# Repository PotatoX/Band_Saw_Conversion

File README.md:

# Band_Saw_Conversion

## Summary

Recently I needed (had an excuse to get) a band saw capable of cutting metal for a few of my projects. As with most of my projects/hobbies there are a number of outcomes I seek:

* Cheap
* Technical
* Build
* Learn

To this end I started shopping around to acquire a band saw as cheap as possible as it would only be used on a limited basis for hobby work. I need the saw to be able to cut metal and fit a small foot print on my bench. I wanted the saw to be vertical in order to minimize the space consumed as my bench and garage space is at a premium at this point.

With these constraints in mind I set my sights on a Harbor Freight 1/3 HP 9 in Benchtop Band Saw. I caught it on sale a Harbor Freight (w/ coupon) for right around $100. Similar saws can be found at your local big box stores.

Using this basic frame and some upgrades I have been able to convert this wood cutting vertical band saw to a metal cutting type with speed control and FPS display.

I now have a small band saw capable of cutting metal, wood, plastic, etc. that fits on the corner of my bench.

This project encompass the conversion and in indented to share the process with other makers. If you have questions, need additional details, or see any bugs please let me know.

The entire project can be found on [GitHub](https://github.com/PotatoX/Band_Saw_Conversion/). Consider contributing and making it even better if you happen to create other customizations.

Additionally, I will list parts used in this project on my [OpenBazzar store](https://openbazaar.com/store/QmVFRGwApdcef56Be7FPXnXQaB79rYrve3otFsrWvSwbAu).

## Design Choices
Thnking ack thrpugh the steps taken from the begining to end; a text book design process was not followed, rather a development and refine!emt from blade to display.

### The Blade
There the first choice was to find a blade that fit and was capable of cutting metalss (steel). By default the saw comes equiped woth a wood cutting 62in blade, carbon steel, 7 Teeth per Inch (*TPI*), 1/8in wide. I had found a couple of reports online that indicate success cutting plastic and aluminium, so long as a gentle touch was used. clearly the default blade had no chance of taking on steels.

Therefore the search began for a suitable bimetal blade. Most of my local stores carried various blades, some bimetal, but none in the 62in size. 62in appears to be a bit of a *custom* size. when local stores fail Amazon.com often saves the day. After scrolling though lists of blades I was able to to find a suitable blade; 62in, bimetal, 1/2in, 14 TPI.

[Imachinist S621214 62-inch X 1/2-inch X 14 TPI Bi-metal Band Saw Blades](https://www.amazon.com/gp/product/B010G9IJG6)

The next challenge was to find a way to drive the blade @ ~300 FPM for Steel, 600ish FPM for Aluminum, and 2000 FPM for Wood. Looking at the stock motor it was designed to drive the blade at 2460 FPM and is not adjustable. Further the motor is an induction motor which can not be speed controlled without a frequency drive, and even with one, would loose power proportional to the reduction in frequency; meaning at slow speeds is would lose power.

Therefore, a SCR controlled DC motor setup was needed. Given the *Cheap* requirement I scrubed ebay for a cheap DC motor. I found that used DC motors from tredmills seem to be abundent and are therefore reasonably priced. I found mine for ~$30.

A small bracket had to be made to adapat the motor to the band saw frame

In order to control the motor I found a generic SCR speed control. The exact feature of the SCR were not necessary to specify other than it needed to be able to handle sufficient power. 4000W was probably over kill, but rather more than not enough, and given the price for smaller units was roughly the same, this did the trick.

The SCR needed a couple of mods to fine tune the upper and lower speed bounds. This is expanded on more in in the electronics section.

In order to install the motor I had a to get small belt pully mate to the motor.

I then needed an clean way to mount the SCR on the frame which led to the need to design an enclosure to house and mount the SCR.

I figured, if I am going to make a custom enclosure might as well make a display to disply the FPM of the blade; I mean I've come this far, why not.

Lastely I designed a small board which reads a hall sensor on the back of the motor, then converts the motor shaft speed to FPM, and displays this on a small 7-Segment output. 

## The Physical Form

### Hardware
The enclosure has been modeled in Onshape, source files can be found [here](https://cad.onshape.com/documents/ca0881e1177c075414a017b7/w/e514d8a98751ae0bca0296ff/e/90af0d38bd02678226dfc615).

If you are in need of a 3D printed enclosure, let me know and I will be happy to add them to my [OpenBazzar store](https://openbazaar.com/store/QmVFRGwApdcef56Be7FPXnXQaB79rYrve3otFsrWvSwbAu).

### Electronics

#### SCR Modifications
Unfortunately I forgot to take pictures while modifing the SCR. If you get a generic SCR you simply have to swap out the the potentiometer some one that is of a range more appropraite for the speeds you whish to operate at. This will be SCR and motor dependent. In my case I added a 33k resistor in series with a 50K pot.

#### Hall Effect Sensor
The hall effect sensor I used was an A3141 IC. This worked for my setup given the magnet I used and its location on the rear portion of the motor shaft. Any hall effect sensor in this family should do the trick.

[Datasheet](https://github.com/PotatoX/Band_Saw_Conversion/blob/master/Electronics/KiCad/Tachometer/Datasheets/A3141-2-3-4-Datasheet.pdf)

#### Tachometer Board
The design has been complete in KiCad. Input either 120V AC or 6V-12V DC. Board can be but down to remove AC section if DC is used. I have excess boards that will be listed on my [OpenBazzar store](https://openbazaar.com/store/QmVFRGwApdcef56Be7FPXnXQaB79rYrve3otFsrWvSwbAu) along with some of the odd components.

If you need a component not currently listed, let me know and I will be happy to add them to my [OpenBazzar store](https://openbazaar.com/store/QmVFRGwApdcef56Be7FPXnXQaB79rYrve3otFsrWvSwbAu) along with some of the odd components..

### Software
[Arduino firmware can be found here.](https://github.com/PotatoX/Band_Saw_Conversion/tree/master/Software/Arduino/Tachometer_Rev_A)

#### Calculation of Slope
There are a couple of ways to calculate the correct [slope value](https://github.com/PotatoX/Band_Saw_Conversion/blob/c9c9d59a0e278d77ea138ab6ab9a776811436fa7/Software/Arduino/Tachometer_Rev_A/Tachometer_Rev_A.ino#L35) for the firmware:

##### Method 1 - Experimentation w/ Tachometer
This method requires a [contactless tachometer](https://www.aliexpress.com/item/2017-Hot-Selling-NEW-Digital-Laser-Photo-Tachometer-Non-Contact-RPM-Tach-Speed-Gauge-Engine-High/32827623720.html).

1. Initially set the slope to 1 and flash the controller.
2. Connect the controller board to the saw and verify proper operation
3. Measure the diameter of one of your blade drive wheels.

4. Place a tachometer reflector on the blade drive wheel and test that stable RPM readings can be taken. **DANGER - _As the cover to the saw is open in order to take this measurement take extream care to be as far away from the blade as possible, and allow yourself multiple options for escape and power shut off incase the blade should come off the drive wheels._**
5. Start the band saw at a low speed and record both the reading on the controller and the reading on the tachometer.
6. Repeat measurements various times in order to take readings through out the intended operating speed range.
7. Using a [spreadsheet](https://github.com/PotatoX/Band_Saw_Conversion/blob/master/Software/Arduino/Tachometer_Rev_A/BandSaw%20Slope%20Calculations.ods?raw=true) convert the tachometer readings to SFM
8. Using a [spreadsheet](https://github.com/PotatoX/Band_Saw_Conversion/blob/master/Software/Arduino/Tachometer_Rev_A/BandSaw%20Slope%20Calculations.ods?raw=true) plot the controller readings vs the SFM(tachometer readings).
10. Generate a linear fit, note the slope of the fit equation.
11. Input the slope into the firmware of the controller and re-flash. The controller should now read in SFM.

##### Method 2 - Ratio Calculations
1. Measure the diameter of one of your blade drive wheels.

2. Count the teeth of the motor pully and the blade wheel pully.
3. Enter the all values in the [spreadsheet](https://github.com/PotatoX/Band_Saw_Conversion/blob/master/Software/Arduino/Tachometer_Rev_A/BandSaw%20Slope%20Calculations.ods?raw=true).
4. Input the slope into the firmware of the controller and flash. The controller should now read in SFM.

# Support Projects Like This
You can support projects like this by using my [OpenBazzar store](https://openbazaar.com/store/QmVFRGwApdcef56Be7FPXnXQaB79rYrve3otFsrWvSwbAu). Like all hobbies, ones that are self-funded are always easier progress.

# Safety/Disclaimer
I am furnishing this item/content "as is". I do not provide any warranty of the item/content whatsoever, whether express, implied, or statutory, including, but not limited to, any warranty of merchantability or fitness for a particular purpose or any warranty that the contents of the item/content will be error-free.

In no respect shall I incur any liability for any damages, including, but limited to, direct, indirect, special, or consequential damages arising out of, resulting from, or any way connected to the use of the item, whether or not based upon warranty, contract, tort, or otherwise; whether or not injury was sustained by persons or property or otherwise; and whether or not loss was sustained from, or arose out of, the results of, the item/content, or any services that may be provided herein.

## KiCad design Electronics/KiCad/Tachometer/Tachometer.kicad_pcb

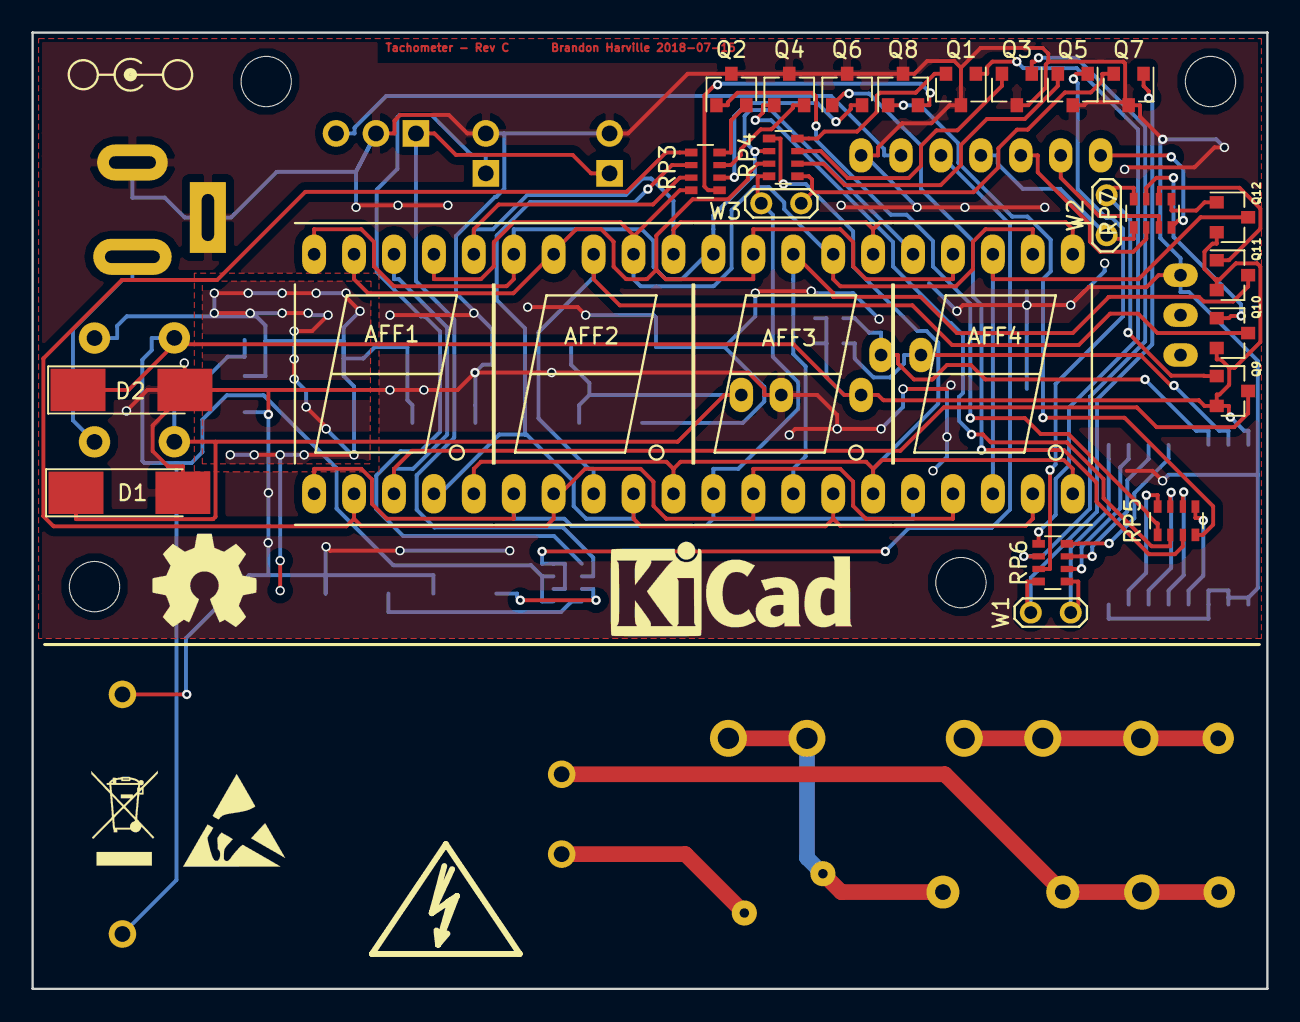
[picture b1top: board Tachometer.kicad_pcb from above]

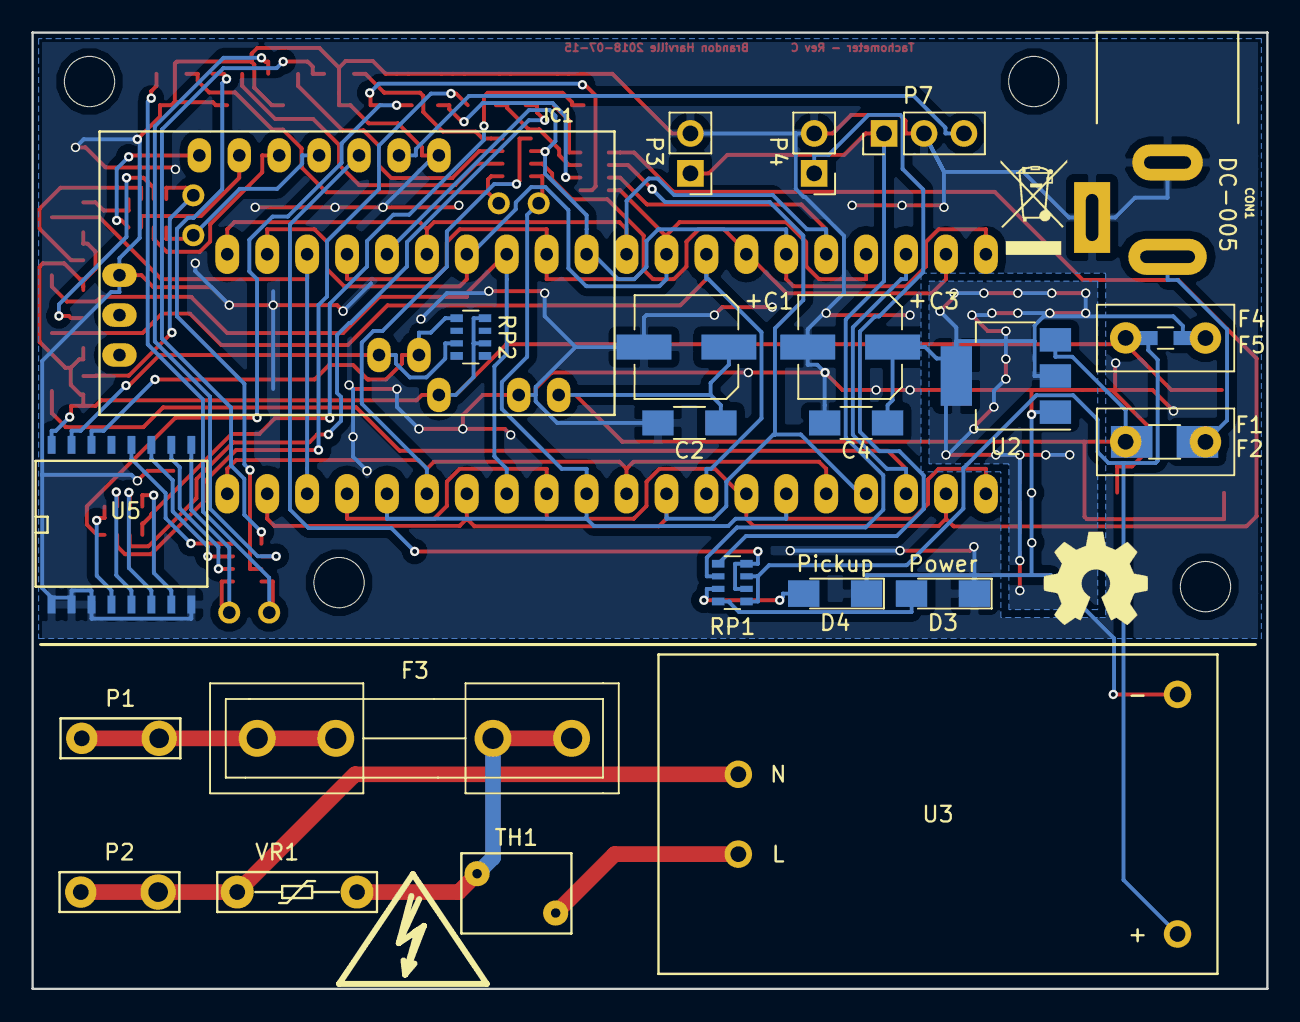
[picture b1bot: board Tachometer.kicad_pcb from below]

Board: 2 copper layers, 78.5 x 60.8 mm, 55 parts (25 on the bottom side), 61 nets.

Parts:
AFF1, AFF2, AFF3, AFF4: LTS-6960HR; 7SegmentLED_LTS6760_LTS6780
C1, C3: 10uF; CP_Elec_6.3x5.3
C2, C4: 22uF; C_1206_HandSoldering
CON1: DC-005; ADC-002
D1: 12V; D_MELF_Handsoldering
D2: 5.1V; D_MELF_Handsoldering
D3: Power; LED_1206_HandSoldering
D4: Pickup; LED_1206_HandSoldering
F1: 1A; Fuse_TE5_Littlefuse-395Series
F2: 2A 16V; Fuse_SMD1206_HandSoldering
F3: 1000mA; Fuseholder5x20_horiz_open_inline_Type-I
F4: 500mA; R_0603_HandSoldering
F5: 500mA; Fuse_TE5_Littlefuse-395Series
IC1: ArduinoProMini; pro_mini
M1, M2, M3, M4: MountingHole_3.2mm_M3_DIN965
P1, P2: CONN_01X01; Male_Terminal_Spade_Connector_6.3_Wide_5.08mm_Pins
P3, P4: CONN_01X02; Pin_Header_Straight_1x02_Pitch2.54mm
P7: CONN_01X03; Pin_Header_Straight_1x03_Pitch2.54mm
Q1, Q2, Q3, Q4, Q5, Q6, Q7, Q8, Q9, Q10, Q11, Q12: MMBT3906; SOT-23
RP1: 150; R_Array_Convex_4x0603
RP2: 10K; R_Array_Convex_4x0603
RP3, RP4: 91; R_Array_Convex_4x0603
RP5, RP6: 100; R_Array_Convex_4x0603
RP7: 510; R_Array_Convex_4x0603
TH1: NTC 5D-7; RV_Disc_D7_W5.1_P5
U2: LM1117-5.0; SOT-223-3_TabPin2
U3: TSP-05; TSP
U5: PCF8574; SO-16-W
VR1: 14D241K 240V; VARISTOR_MCIGICM_14D241K_240V
W1, W2, W3: TEST; Test_Point_2Pads

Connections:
/5V_REG: D2.1, F4.2, F5.2, IC1.21, Q9.2, Q10.2, Q11.2, Q12.2, RP1.1, RP1.3, RP2.2, RP2.4, U3.3, U5.16
/DC_IN: C1.1, C2.1, D1.1, F1.2, F2.2, IC1.24, U2.3
/GND: C1.2, C2.2, C3.2, C4.2, CON1.2, CON1.3, D1.2, D2.2, D3.1, D4.1, IC1.4, IC1.23, IC1.29, P3.2, P4.2, P7.2, Q1.3, Q2.3, Q3.3, Q4.3, Q5.3, Q6.3, Q7.3, Q8.3, U2.1, U3.4, U5.1, U5.2, U5.3, U5.8
/M_LIVE: F3.1, P1.1
/M_NEUTRAL: P2.1, U3.2, VR1.1
unnamed: AFF1.1, AFF2.1, AFF3.1, AFF4.1, RP4.8, W3.2
unnamed: AFF1.2, AFF2.2, AFF3.2, AFF4.2, RP3.5
unnamed: AFF1.3, AFF1.8, Q9.3
unnamed: AFF1.4, AFF2.4, AFF3.4, AFF4.4, RP3.6
unnamed: AFF1.5, AFF2.5, AFF3.5, AFF4.5, RP4.5
unnamed: AFF1.6, AFF2.6, AFF3.6, AFF4.6, RP3.7
unnamed: AFF1.7, AFF2.7, AFF3.7, AFF4.7, RP3.8
unnamed: AFF1.9, AFF2.9, AFF3.9, AFF4.9, RP4.7
unnamed: AFF1.10, AFF2.10, AFF3.10, AFF4.10, RP4.6
unnamed: AFF2.3, AFF2.8, Q10.3
unnamed: AFF3.3, AFF3.8, Q11.3
unnamed: AFF4.3, AFF4.8, Q12.3
unnamed: C3.1, C4.1, F4.1, F5.1, U2.2
unnamed: CON1.1, F1.1, F2.1
unnamed: D3.2, RP1.8
unnamed: D4.2, RP1.7
unnamed: F3.2, TH1.2, VR1.2
unnamed: IC1.5, P7.3
unnamed: IC1.6, RP1.2, RP1.4
unnamed: IC1.7, RP7.1, W2.1
unnamed: IC1.8, RP7.2
unnamed: IC1.9, RP7.3
unnamed: IC1.10, RP7.4
unnamed: IC1.25, RP2.7, U5.15
unnamed: IC1.26, RP2.5, U5.14
unnamed: P3.1, P7.1, RP1.6
unnamed: P4.1, RP1.5
unnamed: Q1.1, RP6.1
unnamed: Q1.2, RP4.4
unnamed: Q2.1, RP5.1
unnamed: Q2.2, RP3.4
unnamed: Q3.1, RP6.2
unnamed: Q3.2, RP4.3
unnamed: Q4.1, RP5.2
unnamed: Q4.2, RP3.3
unnamed: Q5.1, RP6.3
unnamed: Q5.2, RP4.2
unnamed: Q6.1, RP5.3
unnamed: Q6.2, RP3.2
unnamed: Q7.1, RP6.4, W1.1
unnamed: Q7.2, RP4.1, W3.1
unnamed: Q8.1, RP5.4
unnamed: Q8.2, RP3.1
unnamed: Q9.1, RP7.8, W2.2
unnamed: Q10.1, RP7.7
unnamed: Q11.1, RP7.6
unnamed: Q12.1, RP7.5
unnamed: RP5.5, U5.4
unnamed: RP5.6, U5.5
unnamed: RP5.7, U5.6
unnamed: RP5.8, U5.7
unnamed: RP6.5, U5.9, W1.2
unnamed: RP6.6, U5.10
unnamed: RP6.7, U5.11
unnamed: RP6.8, U5.12
unnamed: TH1.1, U3.1

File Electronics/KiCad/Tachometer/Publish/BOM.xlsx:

Id | Designator | Package | Quantity | Designation | Supplier and ref
1 | M1,M2,M4,M3 | MountingHole_3.2mm_M3_DIN965 | 4 | MountingHole_3.2mm_M3_DIN965
2 | REF**,REF** | Symbol_HighVoltage_Type2_CopperTop_VerySmall | 2 | Symbol_HighVoltage_Type2_CopperTop_VerySmall
3 | AFF1,AFF2,AFF3,AFF4 | 7SegmentLED_LTS6760_LTS6780 | 4 | LTS-6960HR
4 | C1,C3 | CP_Elec_6.3x5.3 | 2 | 10uF
5 | C2,C4 | C_1206_HandSoldering | 2 | 22uF
6 | CON1 | ADC-002 | 1 | DC-005
7 | D1 | D_MELF_Handsoldering | 1 | 12V
8 | D2 | D_MELF_Handsoldering | 1 | 5.1V
9 | D3 | LED_1206_HandSoldering | 1 | Power
10 | D4 | LED_1206_HandSoldering | 1 | Pickup
11 | F1 | Fuse_TE5_Littlefuse-395Series | 1 | 1A
12 | F2 | Fuse_SMD1206_HandSoldering | 1 | 2A 16V
13 | F3 | Fuseholder5x20_horiz_open_inline_Type-I | 1 | 1000mA
14 | F4 | R_0603_HandSoldering | 1 | 500mA
15 | F5 | Fuse_TE5_Littlefuse-395Series | 1 | 500mA
16 | P1,P2 | Male_Terminal_Spade_Connector_6.3_Wide_5.08mm_Pins | 2 | CONN_01X01
17 | P3,P4 | Pin_Header_Straight_1x02_Pitch2.54mm | 2 | CONN_01X02
18 | RP1 | R_Array_Convex_4x0603 | 1 | 150
19 | RP2 | R_Array_Convex_4x0603 | 1 | 10K
20 | RP3,RP4 | R_Array_Convex_4x0603 | 2 | 91
21 | TH1 | RV_Disc_D7_W5.1_P5 | 1 | NTC 5D-7
22 | U2 | SOT-223-3_TabPin2 | 1 | LM1117-5.0
23 | U5 | SO-16-W | 1 | PCF8574
24 | VR1 | VARISTOR_MCIGICM_14D241K_240V | 1 | 14D241K 240V
25 | IC1 | pro_mini | 1 | ArduinoProMini
26 | U3 | TSP | 1 | TSP-05
27 | P7 | Pin_Header_Straight_1x03_Pitch2.54mm | 1 | CONN_01X03
28 | Q1,Q2,Q3,Q4,Q5,Q6,Q7,Q8,Q9,Q10,Q11,Q12 | SOT-23 | 12 | MMBT3906
29 | RP5,RP6 | R_Array_Convex_4x0603 | 2 | 100
30 | RP7 | R_Array_Convex_4x0603 | 1 | 510
31 | W1,W2,W3 | Test_Point_2Pads | 3 | TEST
32 | REF*** | KiCad-Logo_6mm_SilkScreen | 1 | KiCad-Logo_6mm_SilkScreen
33 | REF** | Symbol_Barrel_Polarity | 1 | Symbol_Barrel_Polarity
34 | REF***,REF*** | OSHW-Symbol_6.7x6mm_SilkScreen | 2 | OSHW-Symbol_6.7x6mm_SilkScreen
35 | REF*** | ESD-Logo_6.6x6mm_SilkScreen | 1 | ESD-Logo_6.6x6mm_SilkScreen
36 | REF***,REF*** | WEEE-Logo_4.2x6mm_SilkScreen | 2 | WEEE-Logo_4.2x6mm_SilkScreen

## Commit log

2018-08-27 Intial uploads of project
2018-08-27 More uploads
2018-08-27 More initial uploads
2018-08-27 Added hyperlinks
2018-08-27 Adding blade detail
2018-08-30 Updated images
    Update image links
2018-08-30 Add diclaimer
2018-08-30 More updates
2018-08-31 Updates to Hardware
2018-08-31 Additional updates
2018-08-31 More models
2018-09-23 Slope Instruction
2018-09-23 Add code of conduct
2018-09-23 Update issue templates
